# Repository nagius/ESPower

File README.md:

# ESPower

ESPower is a motherboard for ESP8266-01 with voltage regulator, voltage protection and Li-Ion battery charger integrated. 

It has been designed to run off intermittent 5V USB power supply but it can also be powerred by a small 6V Solar panels. Low power consumption has been kept in mind.

The narrow form factor has been designed to be embedded in small upcycled objects like used glass bottles.

## Features

- Li-Ion battery charger with battery protection (TP4056).
- Intensity of battery recharge can be selected between 250mA and 1A with solder jumpers.
- Power path to select if the board is always powered by the battery or is also powered by VCC when an external power supply is provided.
- Voltage detector to properly switch off the ESP8266 when the battery voltage is too low for proper operation. This prevent crashes of the ESP when the battery is drained.
- Voltage detector signal is exported so it can be used by any attached components, like boost-buck converters to shut them down if the battery voltage is too low.

## Manufacturing

See directory `Gerber/` for production files and bill of materials.

## Versions

Version 2 has been slightly improved with a smaller form-factor, Tantalum capacitors to reduce thickness and pull-up resistors on GPIOs to ensure proper boot of the ESP.

## License

Copyleft 2022-2024 - Nicolas AGIUS

Creative Commons - Attribution-NonCommercial-ShareAlike 4.0 International (CC BY-NC-SA 4.0)

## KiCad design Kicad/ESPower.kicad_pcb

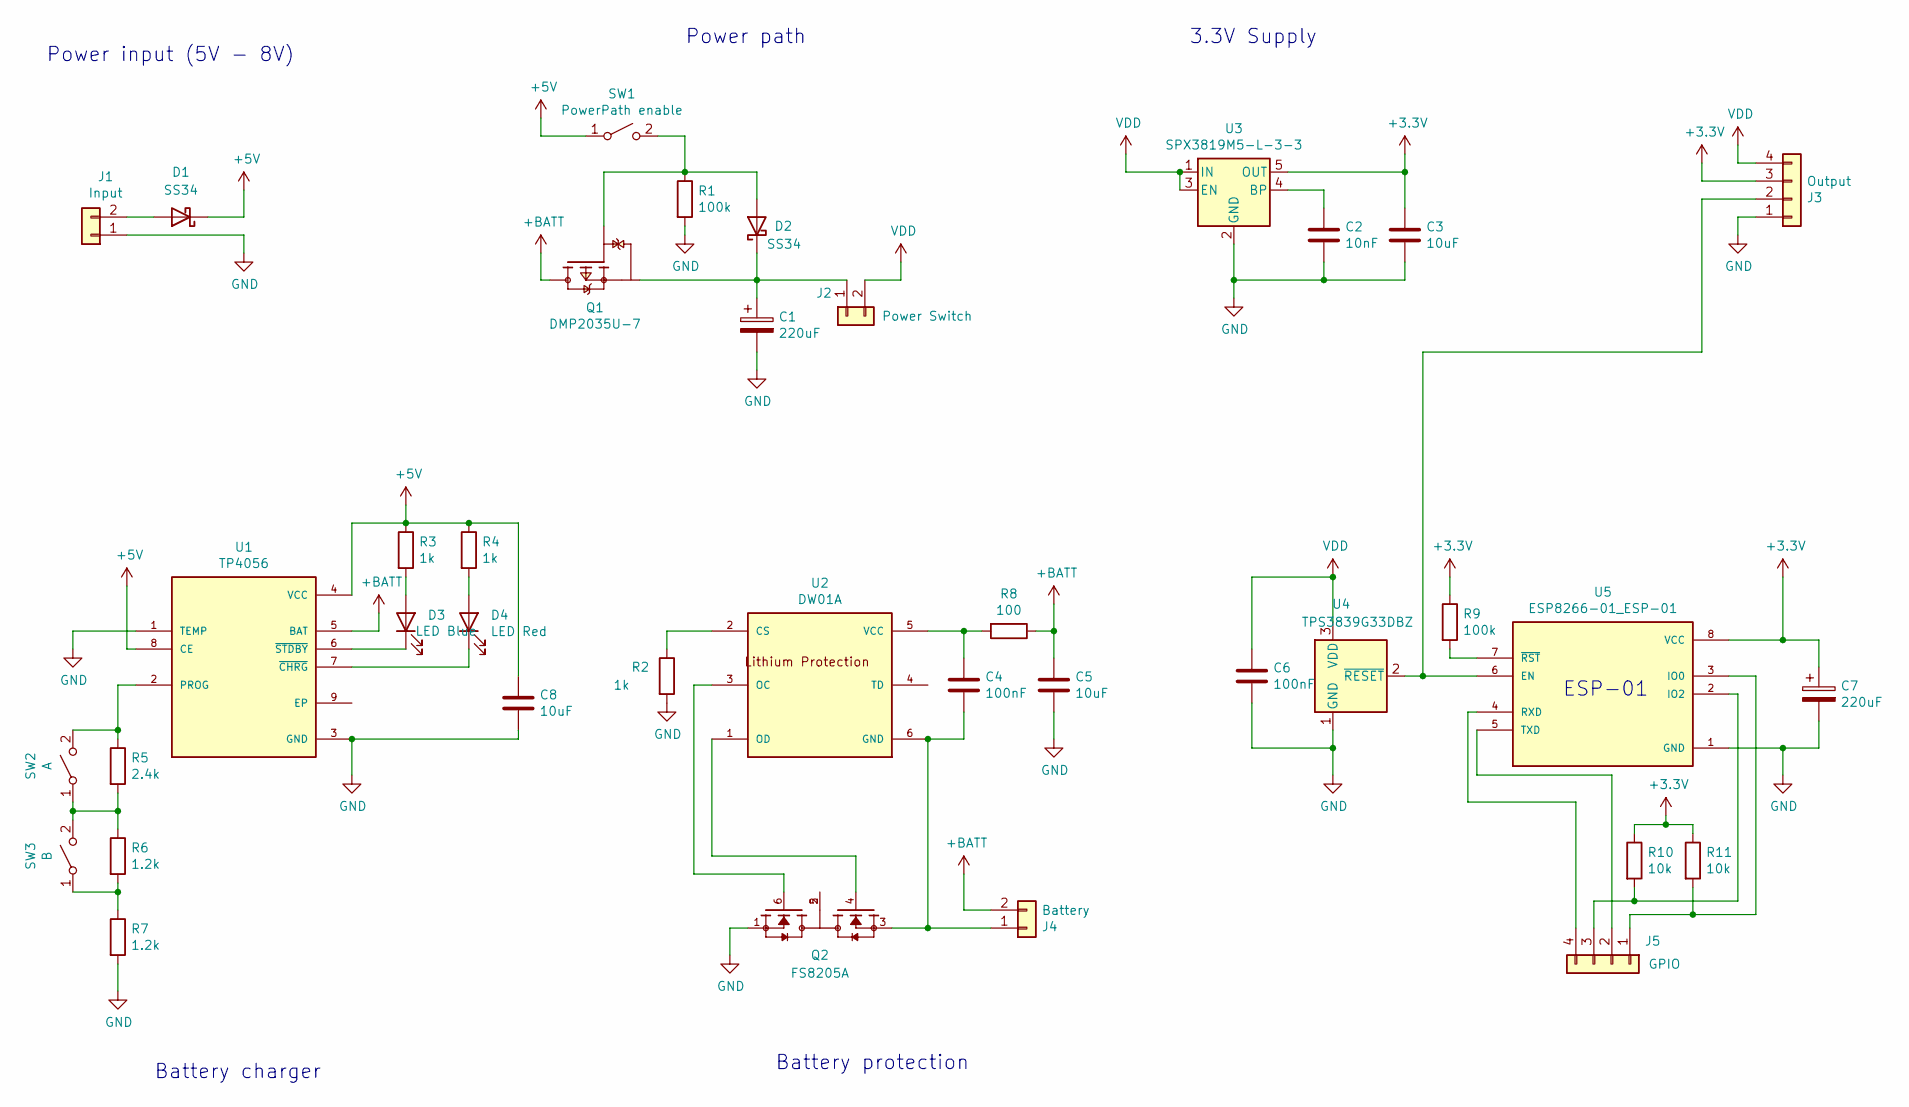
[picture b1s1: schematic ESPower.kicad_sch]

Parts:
C1, C7: 220uF; CP_EIA-6032-28_Kemet-C; LCSC C123271
C2: 10nF; C_0603_1608Metric; LCSC C57112
C3, C5, C8: 10uF; C_0603_1608Metric; LCSC C19702
C4, C6: 100nF; C_0603_1608Metric; LCSC C14663
D1, D2: SS34; D_SMA; LCSC C8678
D3: LED Blue; LED_0603_1608Metric; LCSC C2288
D4: LED Red; LED_0603_1608Metric; LCSC C2286
J1: Input; PinHeader_1x02_P2.54mm_Vertical
J2: Power Switch; PinHeader_1x02_P2.54mm_Vertical
J3: Output; PinHeader_1x04_P2.54mm_Vertical
J4: Battery; PinHeader_1x02_P2.54mm_Vertical
J5: GPIO; PinHeader_1x04_P2.54mm_Vertical
Q1: DMP2035U-7; SOT-23; LCSC C110499
Q2: FS8205A; SOT-23-6; LCSC C2830320
R1, R9: 100k; R_0603_1608Metric; LCSC C25803
R2, R3, R4: 1k; R_0603_1608Metric; LCSC C21190
R5: 2.4k; R_0603_1608Metric; LCSC C22940
R6, R7: 1.2k; R_0603_1608Metric; LCSC C22765
R8: 100; R_0603_1608Metric; LCSC C22775
R10, R11: 10k; R_0603_1608Metric; LCSC C25804
SW1: PowerPath enable; SolderJumper-2_P1.3mm_Open_TrianglePad1.0x1.5mm
SW2: A; SolderJumper-2_P1.3mm_Open_TrianglePad1.0x1.5mm
SW3: B; SolderJumper-2_P1.3mm_Open_TrianglePad1.0x1.5mm
U1: TP4056; HTSOP-8-1EP_3.9x4.9mm_P1.27mm_EP2.4x3.2mm; LCSC C16581
U2: DW01A; SOT-23-6; LCSC C351410
U3: SPX3819M5-L-3-3; SOT-23-5; LCSC C9055
U4: TPS3839G33DBZ; SOT-23; LCSC C485802
U5: ESP8266-01_ESP-01; XCVR_ESP8266-01_ESP-01

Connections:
+3V3: C3.1, C7.1, J3.3, R9.1, R10.1, R11.1, U3.5 (OUT), U5.8 (VCC)
+5V: C8.1, D1.1 (K), R3.1, R4.1, SW1.1 (A), U1.4 (VCC), U1.8 (CE)
+BATT: C5.1, J4.2, Q1.3, R8.1, U1.5 (BAT)
GND: C1.2, C2.2, C3.2, C5.2, C6.2, C7.2, C8.2, J1.1, J3.1, Q2.1, R1.2, R2.2, R7.2, U1.1 (TEMP), U1.3 (GND), U3.2 (GND), U4.1 (GND), U5.1 (GND)
unnamed: C1.1, D2.1 (K), J2.1, Q1.2
unnamed: C2.1, U3.4 (BP)
unnamed: C4.1, R8.2, U2.5 (VCC)
unnamed: C4.2, J4.1, Q2.3, U2.6 (GND)
unnamed: D1.2 (A), J1.2
unnamed: D2.2 (A), Q1.1, R1.1, SW1.2 (B)
unnamed: D3.1 (K), U1.6 (~STDBY)
unnamed: D3.2 (A), R3.2
unnamed: D4.1 (K), U1.7 (~CHRG)
unnamed: D4.2 (A), R4.2
unnamed: J3.2, U4.2 (~RESET), U5.6 (EN)
unnamed: J5.1, R11.2, U5.3 (IO0)
unnamed: J5.2, U5.5 (TXD)
unnamed: J5.3, R10.2, U5.2 (IO2)
unnamed: J5.4, U5.4 (RXD)
unnamed: Q2.2, Q2.5
unnamed: R2.1, U2.2 (CS)
unnamed: R5.1, SW2.2 (B), U1.2 (PROG)
unnamed: R5.2, R6.1, SW2.1 (A), SW3.2 (B)
unnamed: R6.2, R7.1, SW3.1 (A)
unnamed: R9.2, U5.7 (~RST)
unnamed: Q2.4, U2.1 (OD)
unnamed: Q2.6, U2.3 (OC)
VDD: C6.1, J2.2, J3.4, U3.1 (IN), U3.3 (EN), U4.3 (VDD)

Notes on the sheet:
3.3V Supply
ESP-01
Battery charger
Power input (5V - 8V)
Battery protection
Power path

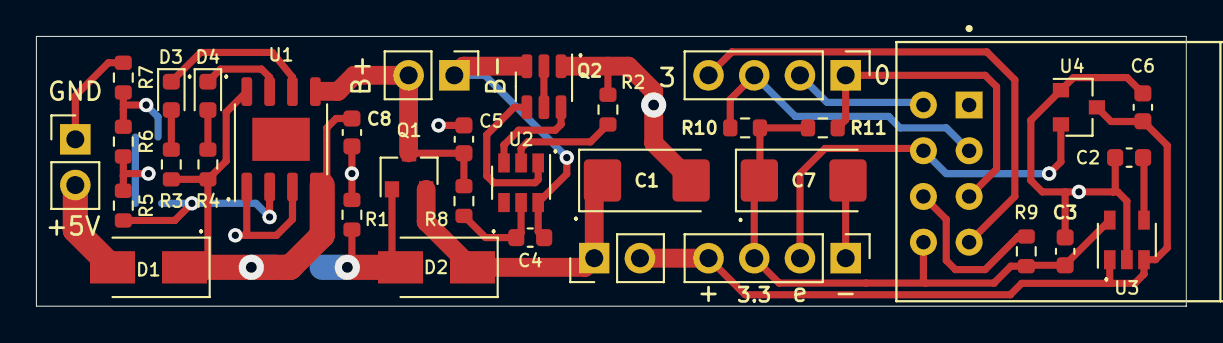
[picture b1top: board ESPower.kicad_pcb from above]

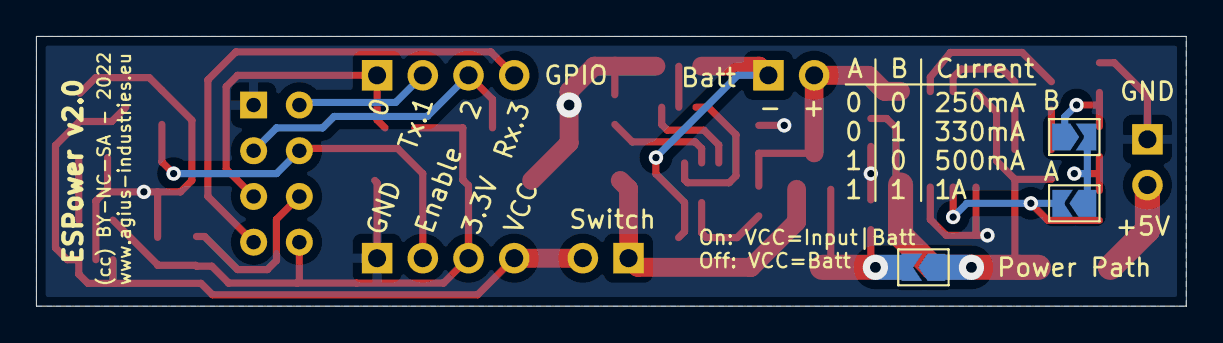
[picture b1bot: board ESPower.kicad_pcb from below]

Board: 2 copper layers, 63.9 x 15.0 mm, 38 parts (3 on the bottom side), 28 nets.

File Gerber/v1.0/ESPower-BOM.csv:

Comment,Designator,Footprint,LCSC
"10nF","C2","Capacitor_SMD:C_0603_1608Metric","C57112"
"10uF","C3","Capacitor_Tantalum_SMD:CP_EIA-3216-10_Kemet-I","C7171"
"10uF","C5","Capacitor_SMD:C_0603_1608Metric","C19702"
"100nF","C4,C6","Capacitor_SMD:C_0603_1608Metric","C14663"
"SS34","D1,D2","Diode_SMD:D_SMA","C8678"
"LED Blue","D3","LED_SMD:LED_0603_1608Metric","C72041"
"LED Red","D4","LED_SMD:LED_0603_1608Metric","C2286"
"DMP2035U-7","Q1","Package_TO_SOT_SMD:SOT-23","C110499"
"FS8205A","Q2","Package_SO:TSSOP-8_4.4x3mm_P0.65mm","C16052"
"100k","R1,R9","Resistor_SMD:R_0603_1608Metric","C25803"
"1k","R2,R3,R4","Resistor_SMD:R_0603_1608Metric","C21190"
"2.4k","R5","Resistor_SMD:R_0603_1608Metric","C22940"
"1.2k","R6,R7","Resistor_SMD:R_0603_1608Metric","C22765"
"100","R8","Resistor_SMD:R_0603_1608Metric","C22775"
"TP4056","U1","Package_SO:HTSOP-8-1EP_3.9x4.9mm_P1.27mm_EP2.4x3.2mm","C16581"
"DW01A","U2","Package_TO_SOT_SMD:SOT-23-6","C351410"
"SPX3819M5-L-3-3","U3","Package_TO_SOT_SMD:SOT-23-5","C9055"
"TPS3839G33DBZ","U4","Package_TO_SOT_SMD:SOT-23","C485802"

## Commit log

2022-09-21 First draft
2022-09-21 Updated labels
2022-09-21 Moved GND vias
2022-09-24 Added routing
2022-09-26 Final routing
2022-09-27 Pre-reorganization
2022-09-28 pre-change diode
2022-09-29 Switched diodes to SS34C
2023-01-09 Version 1.0
2024-07-21 Update to KiCad v6
2024-07-21 Added Datasheets and docs
2024-07-21 Added License
2024-08-06 Improved schematic
2024-08-14 Resized board
2024-08-15 Finalized silkscreen
2024-08-22 Switched Q2 footprint
2024-09-03 Updated license
